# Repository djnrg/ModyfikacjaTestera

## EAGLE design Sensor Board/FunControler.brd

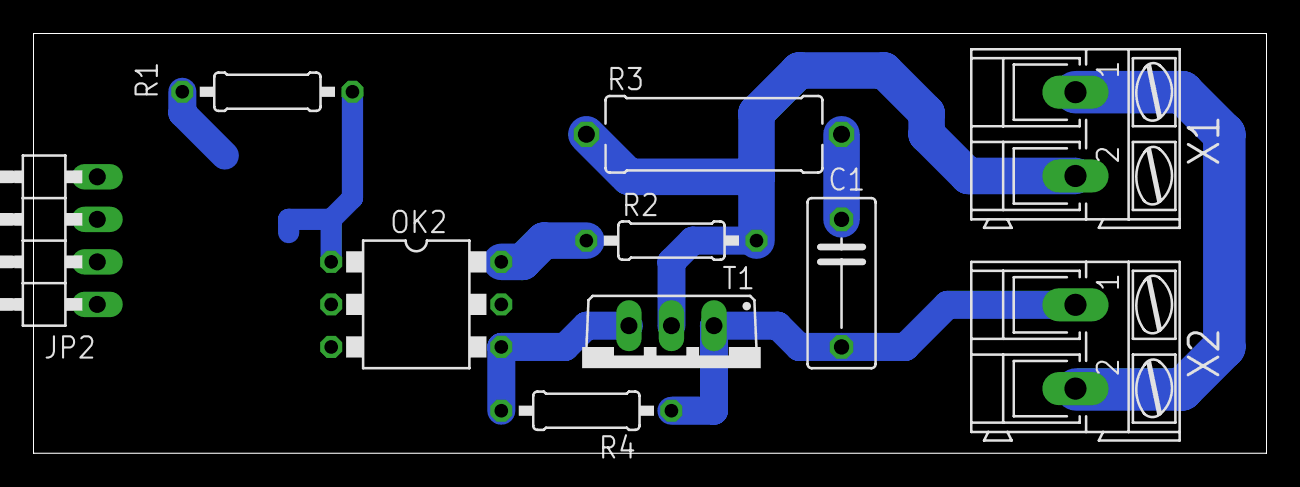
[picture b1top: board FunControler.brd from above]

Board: 2 copper layers, 73.6 x 25.1 mm, 13 parts (1 on the bottom side), 9 nets.

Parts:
C1: 100nF (630V); C075-042X103
DRILEGEND: DRILEGEND
JP2: Connector; 1X04/90
LED1: SML1206
OK2: MOC3041T; DIL06B
R1: 1K; 0207/10
R2: 360; 0207/10
R3: 100 (1/2W); P0613/15
R4: 330; 0207/10
T1: BT138-V; TO220BV
U$1: A5L-LOC
X1: FunOut; AK300/2
X2: AC IN; AK300/2

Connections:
GND: JP2.1, LED1.C, OK2.2
unnamed: JP2.4, R1.1
unnamed: X1.1, X2.2
unnamed: LED1.A, OK2.1, R1.2
unnamed: C1.2, R4.1, T1.T1, X2.1
unnamed: OK2.4, R4.2, T1.G
unnamed: OK2.6, R2.1
unnamed: R2.2, R3.1, T1.T2, X1.2
unnamed: C1.1, R3.2

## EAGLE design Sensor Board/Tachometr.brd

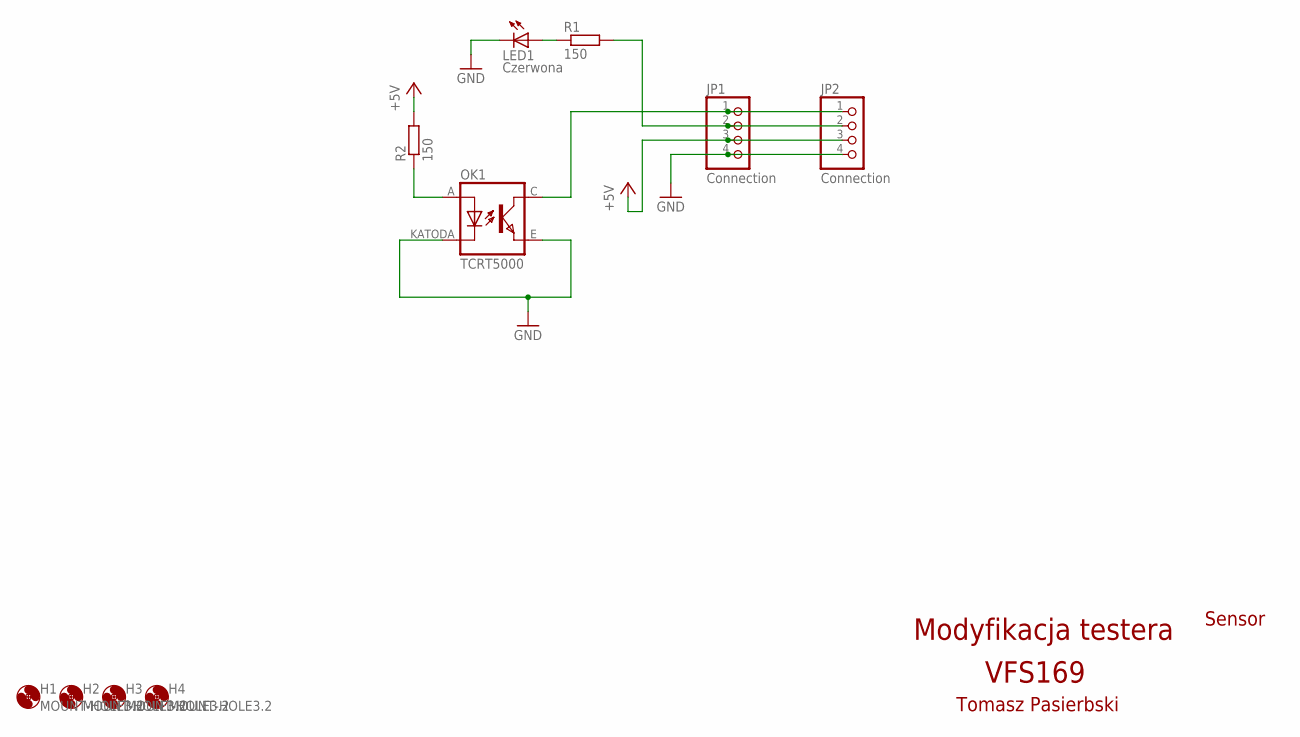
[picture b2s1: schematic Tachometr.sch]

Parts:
H1, H2, H3, H4: MOUNT-HOLE3.2; 3,2
JP1: Connection; 1X04/90
JP2: Connection; 1X04
LED1: Czerwona; CHIPLED_1206
OK1: TCRT5000
R1, R2: 150; R1206

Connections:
+5V: JP1.3, JP2.3, R2.2
GND: JP1.4, JP2.4, LED1.C, OK1.E (EMITTER), OK1.KATODA (CATHODE)
unnamed: OK1.A (ANODE), R2.1
unnamed: LED1.A, R1.1
unnamed: JP1.2, JP2.2, R1.2
unnamed: JP1.1, JP2.1, OK1.C (COLLECTOR)

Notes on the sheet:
Modyfikacja testera
VFS169
Tomasz Pasierbski
Sensor

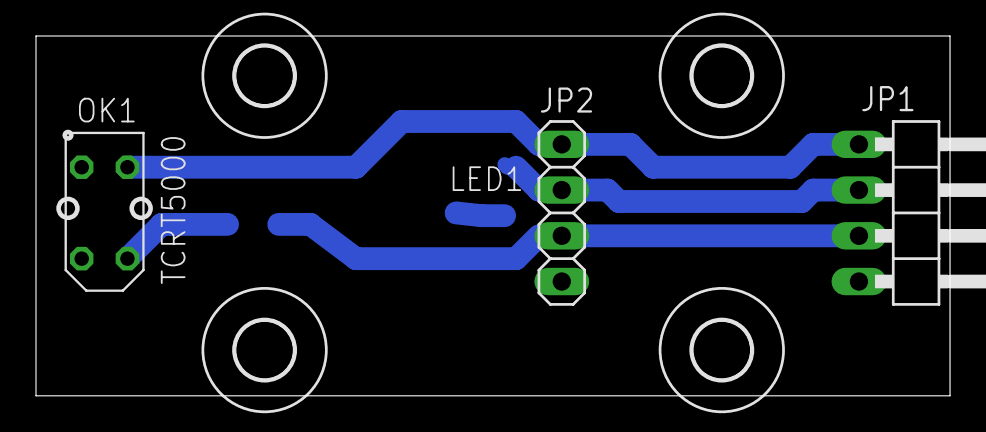
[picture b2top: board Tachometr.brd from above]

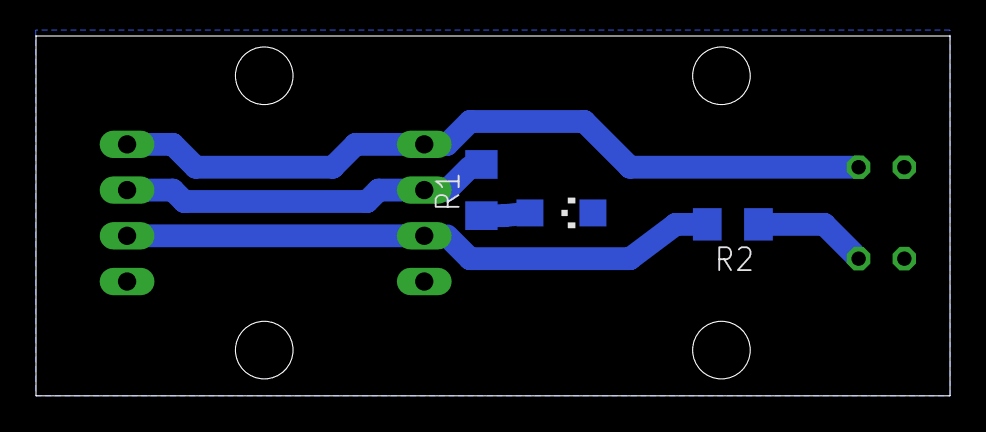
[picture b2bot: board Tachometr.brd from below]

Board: 2 copper layers, 50.8 x 20.0 mm, 12 parts (3 on the bottom side), 6 nets.

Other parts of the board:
DRILEGEND: DRILEGEND
U$1: A5L-LOC

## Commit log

2016-01-15 :neckbeard: Added .gitattributes
2016-01-15 Start programing
    Beginning solution
2016-01-16 Zarzadzanie katalogami
    Dodanie zarzdzanie katalogami
2016-01-17 Zmiana wyswietlania dodatkowych form
    Przeniesienie ACLoop oraz Chart na forę MAIN
2016-01-17 Połaczenie danych do kontrolek
    przypisanie zmiennych z kontrolek
2016-01-19 Wykres
    Dodanie obsługi wykresu release ALPHA
2016-01-20 Release 0.7.05
    Release 0.7.05 - Working on test!
2016-01-24 Release 0.7.8
    Working on test
2016-07-19 Add Data
    Updated project with sensor board and Arduino Code
2016-07-19 Release 1.0.0
    Add image from release 1.0.0
